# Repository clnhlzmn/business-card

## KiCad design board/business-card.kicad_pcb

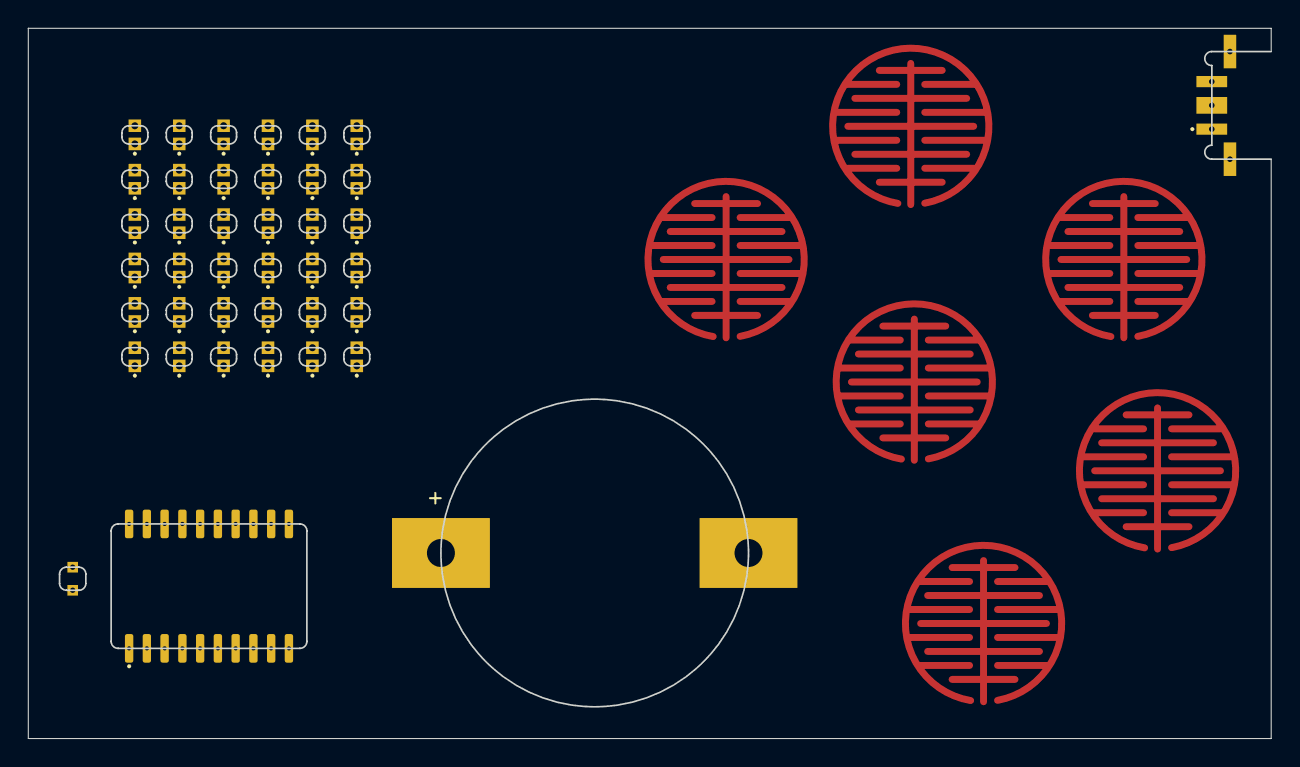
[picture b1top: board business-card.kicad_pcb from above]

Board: 2 copper layers, 88.9 x 50.7 mm, 47 parts (1 on the bottom side), 21 nets, no tracks yet.

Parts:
BT1: Battery_Cell; CR2016_MFR_SM_through_board_mount
C2: 0.1 uF; 0603_through_board_mount
D1, D2, D3, D4, D5, D6, D7, D8, D9, D10, D11, D12, D13, D14, D15, D16, D17, D18, D19, D20, D21, D22, D23, D24, D25, D26, D27, D28, D29, D30, D31, D32, D33, D34, D35, D36: LED; XZCBD53W-6_through_board_mount
J1: Conn_01x06; Molex_788641001_mating_pad_layout
SW1: SW_SPDT; JSX08001SAQNL_through_board_mount
SW2, SW3, SW4, SW5, SW6, SW7: Mutual_Capacitance_Button
U1: ATtiny1616-S; SOIC-20W_7.5x12.8mm_P1.27mm_through_board_mount

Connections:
/COL0: D1.2, D2.2, D9.2, D10.2, D17.2, D26.2
/COL1: D3.2, D4.2, D11.2, D12.2, D18.2, D27.2
/COL2: D5.2, D6.2, D13.2, D14.2, D19.2, D28.2
/COL3: D7.2, D8.2, D15.2, D16.2, D20.2, D29.2
/COL4: D21.2, D22.2, D23.2, D24.2, D25.2, D30.2
/COL5: D31.2, D32.2, D33.2, D34.2, D35.2, D36.2
/GND: BT1.2, C2.2, J1.6, U1.20
/ROW0: D1.1, D3.1, D5.1, D7.1, D21.1, D31.1
/ROW1: D2.1, D4.1, D6.1, D8.1, D22.1, D32.1
/ROW2: D9.1, D11.1, D13.1, D15.1, D23.1, D33.1
/ROW3: D10.1, D12.1, D14.1, D16.1, D24.1, D34.1
/ROW4: D17.1, D18.1, D19.1, D20.1, D25.1, D35.1
/ROW5: D26.1, D27.1, D28.1, D29.1, D30.1, D36.1
/UPDI_DATA: J1.2, U1.16
/VDD: C2.1, J1.1, SW1.3, U1.1
/X0: SW3.1, SW5.1
/X1: SW2.1, SW7.1
/X2: SW4.1, SW6.1
/Y0: SW2.2, SW3.2, SW5.2
/Y1: SW4.2, SW6.2, SW7.2
unnamed: BT1.1, SW1.2

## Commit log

2019-11-09 add new kicad project for board
2019-11-10 add stm8s and kx003 to schematic
2019-11-10 modify sym-lib-table
2019-11-10 schematic
2019-11-11 start adding led matrix
2019-11-12 finish led matrix
2019-11-13 add footprints and start schematic (still need connector footprint)
2019-11-13 layout leds, add cam to ignore
2019-11-14 rotate leds and arrange resistors
2021-05-03 Updated gitignore.
2021-05-04 Changed mcu to attiny (for cap touch), removed led resistors (not going to need them), changed switch symbol.
2021-05-05 Changed programming connector to updi pinout.
2021-05-06 Added another row and column of leds, and buttons.
2021-05-06 Annotated board, added some part numbers and footprints.
2021-05-07 Added footprint for programming connector and added programming adapter board project.
2021-05-08 Updated footprints for mcu and switch.
2021-05-08 Removed unused project specific footprint and symbol libs.
2021-05-08 Added business card specific footprints to business-card.pretty lib.
2021-05-08 Added through board footprint for XZCBD led.
2021-05-10 Added 0603 through board mount, arranged leds in grid.
2021-05-11 Added another row and column of leds.
